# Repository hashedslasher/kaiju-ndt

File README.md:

# Kaiju U-NDT

This is my team's EE senior design project. It is in very early development and will evolve into an autonomous immersion UT device.
The [pic0rick](https://github.com/kelu124/pic0rick) is used for the pulser/receiver, and the V1 Engineering [MPCNC](https://docs.v1e.com/mpcnc/intro) will be used for xyz gantry

The name Kaiju came from a toy that randomly appeared in our lab one day

## Development
   If you are working on this project see [Setup](setup/README.md)

## To run the python scripts

1. **Clone the repo**
   Clone the repo (or download as zip) and cd into kaiju-ndt.

2. **Install Python and dependencies**
   - **Windows:** Download from [python.org](https://www.python.org/downloads/windows/) or run:
     ```bash
     winget install -e --id python.python.3.14
     ```
   - **MacOS:** Download from [python.org](https://www.python.org/downloads/macos/) or run:
     ```bash
     brew install python3
     ```
   - **Linux:** Install python with your package manager:
   
   Debian based:
   ```bash
   sudo apt install python3 python3-pip
   ```
   Arch:
   ```bash
   sudo pacman -S python python-pip
   ```
### Python dependencies
   - Open PowerShell or Terminal and run:
     ```bash
     pip install -r python-tools/requirements.txt
     ```

3. **Flashing the firmware**
   - If the firmware isn't already on the pico, you need to flash it.
   - Hold `BOOTSEL` and plug the board in. It should appear as `RPI-RP2`.
   - Drag and drop `firmware/pico/rp2040.uf2` (Pico) or `firmware/pico/rp2350.uf2` (Pico 2) into the `RPI-RP2` drive.
   - Or with picotool from the root of the repository:
   ```bash
   picotool load firmware/pico/rp2040.uf2
   ```

4. **Run a script**
   In PowerShell or Terminal:
   ```bash
   python3 python-tools/{script_name}.py
   ```

   If you use nix for some reason just:
   ```bash
   nix develop .
   python3 python-tools/{script_name}.py
   ```

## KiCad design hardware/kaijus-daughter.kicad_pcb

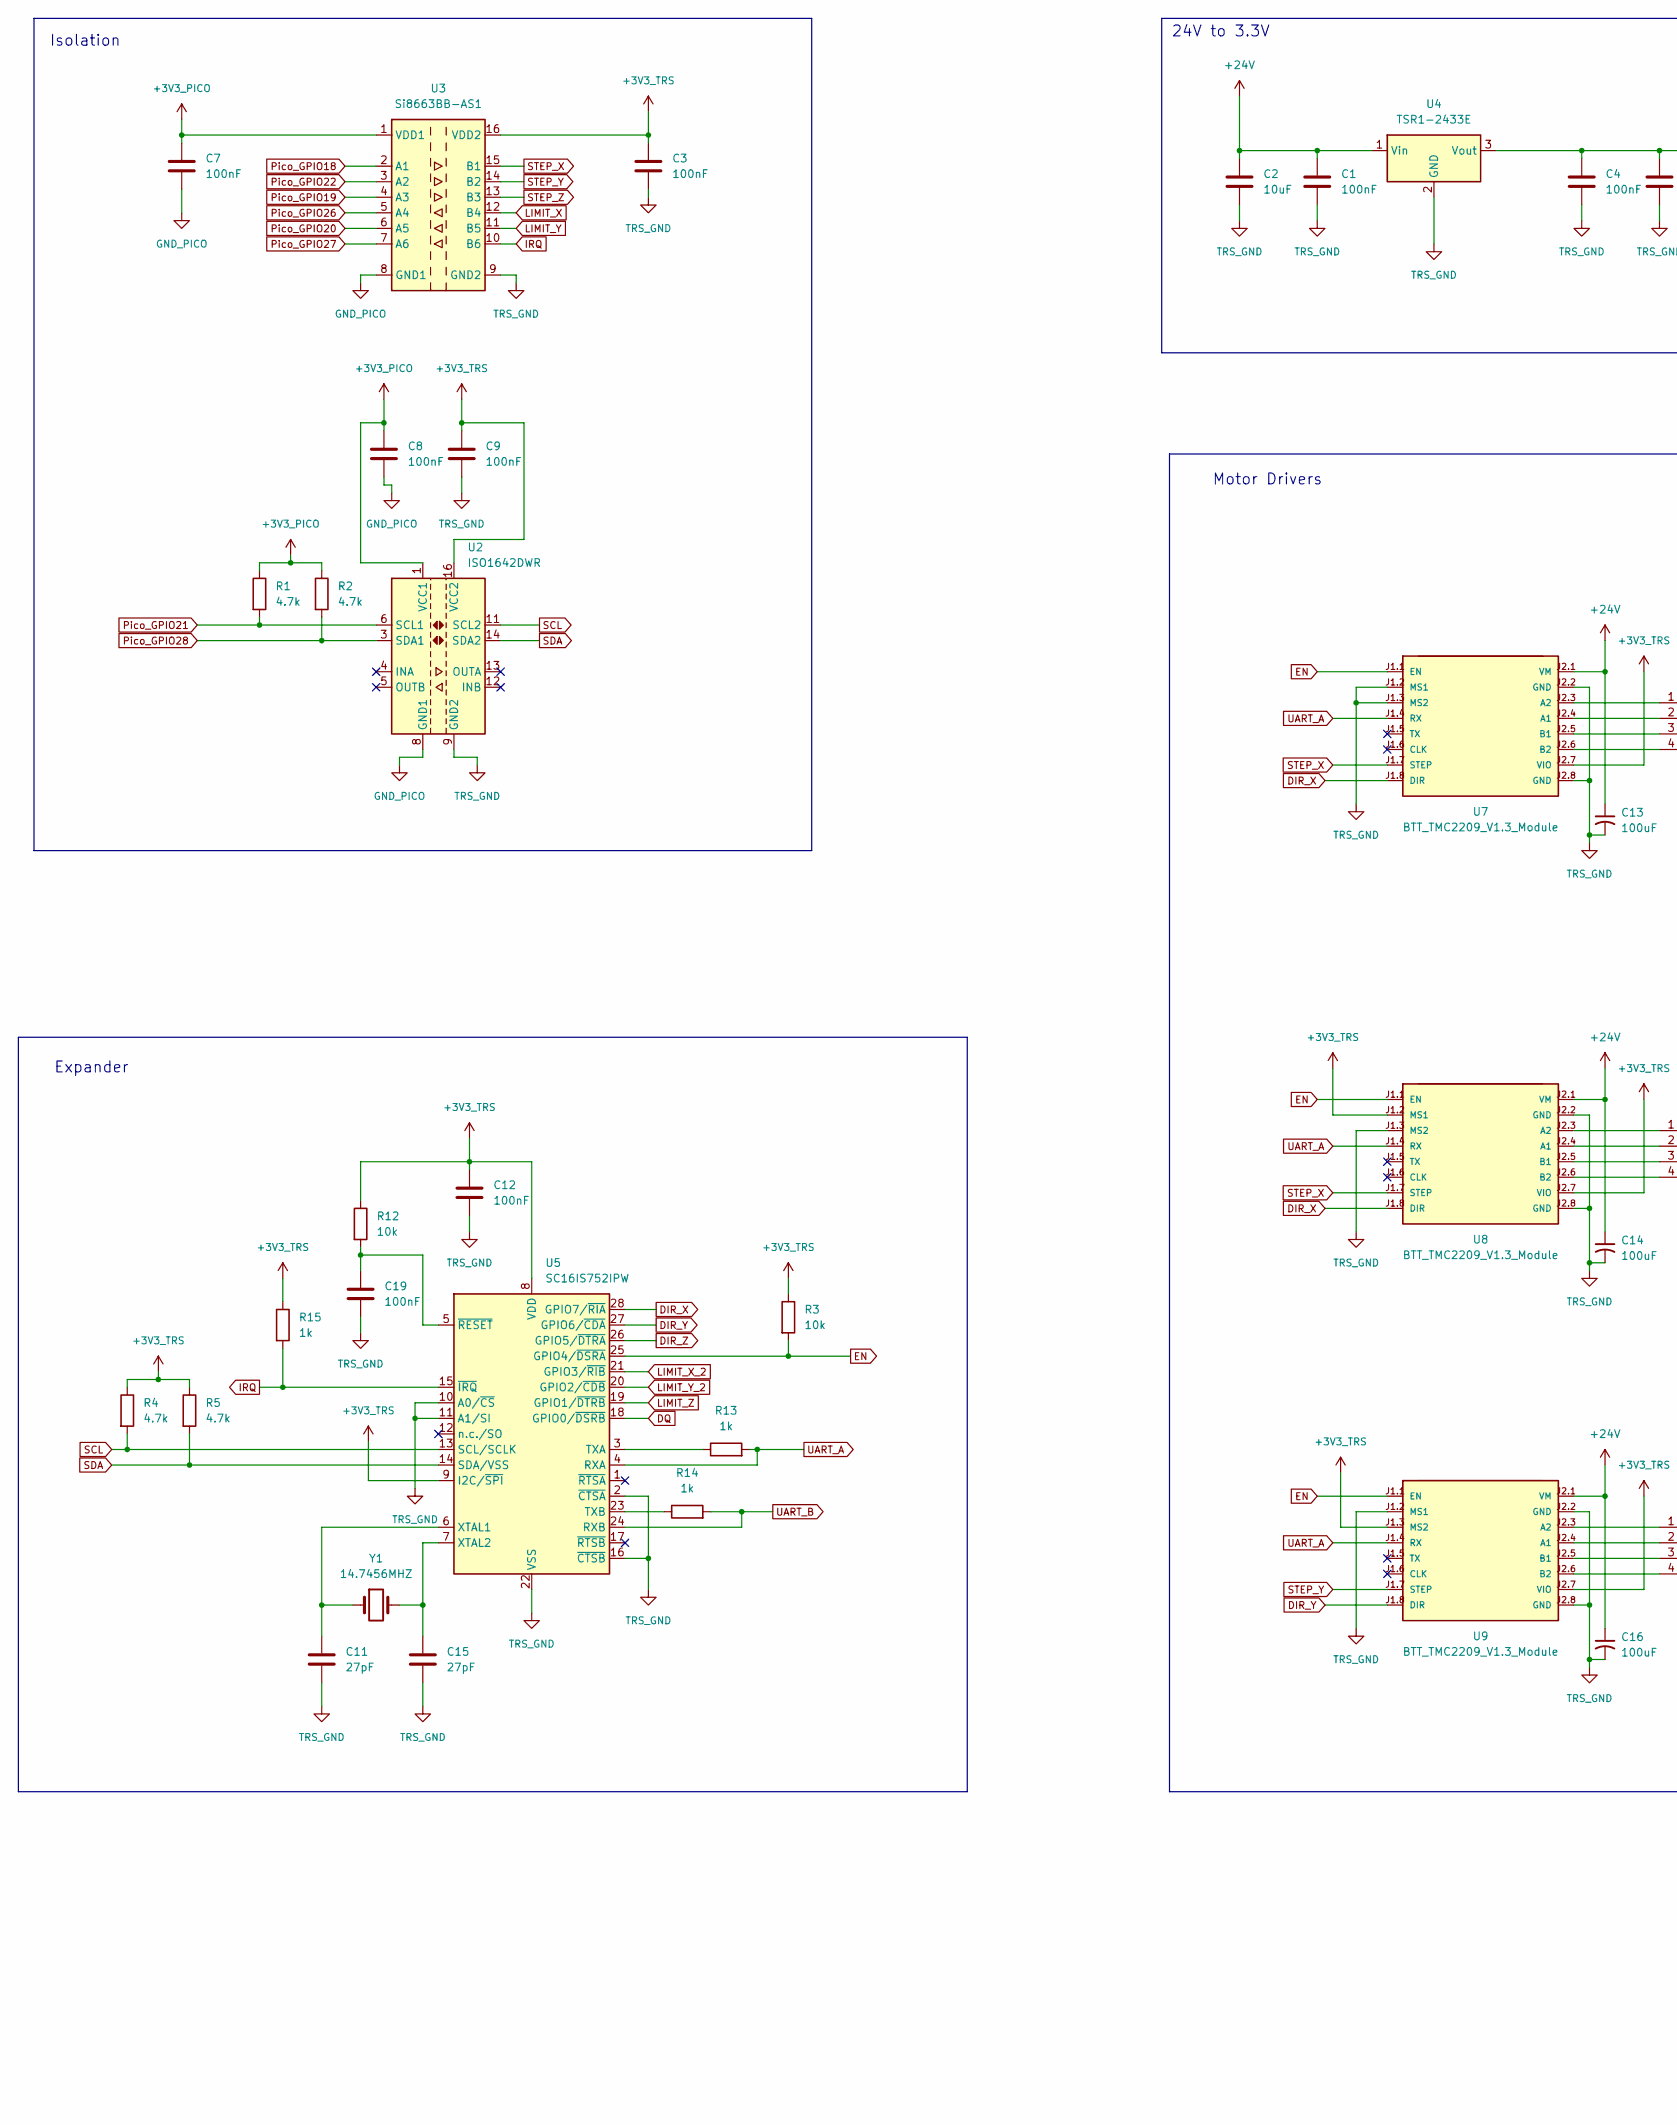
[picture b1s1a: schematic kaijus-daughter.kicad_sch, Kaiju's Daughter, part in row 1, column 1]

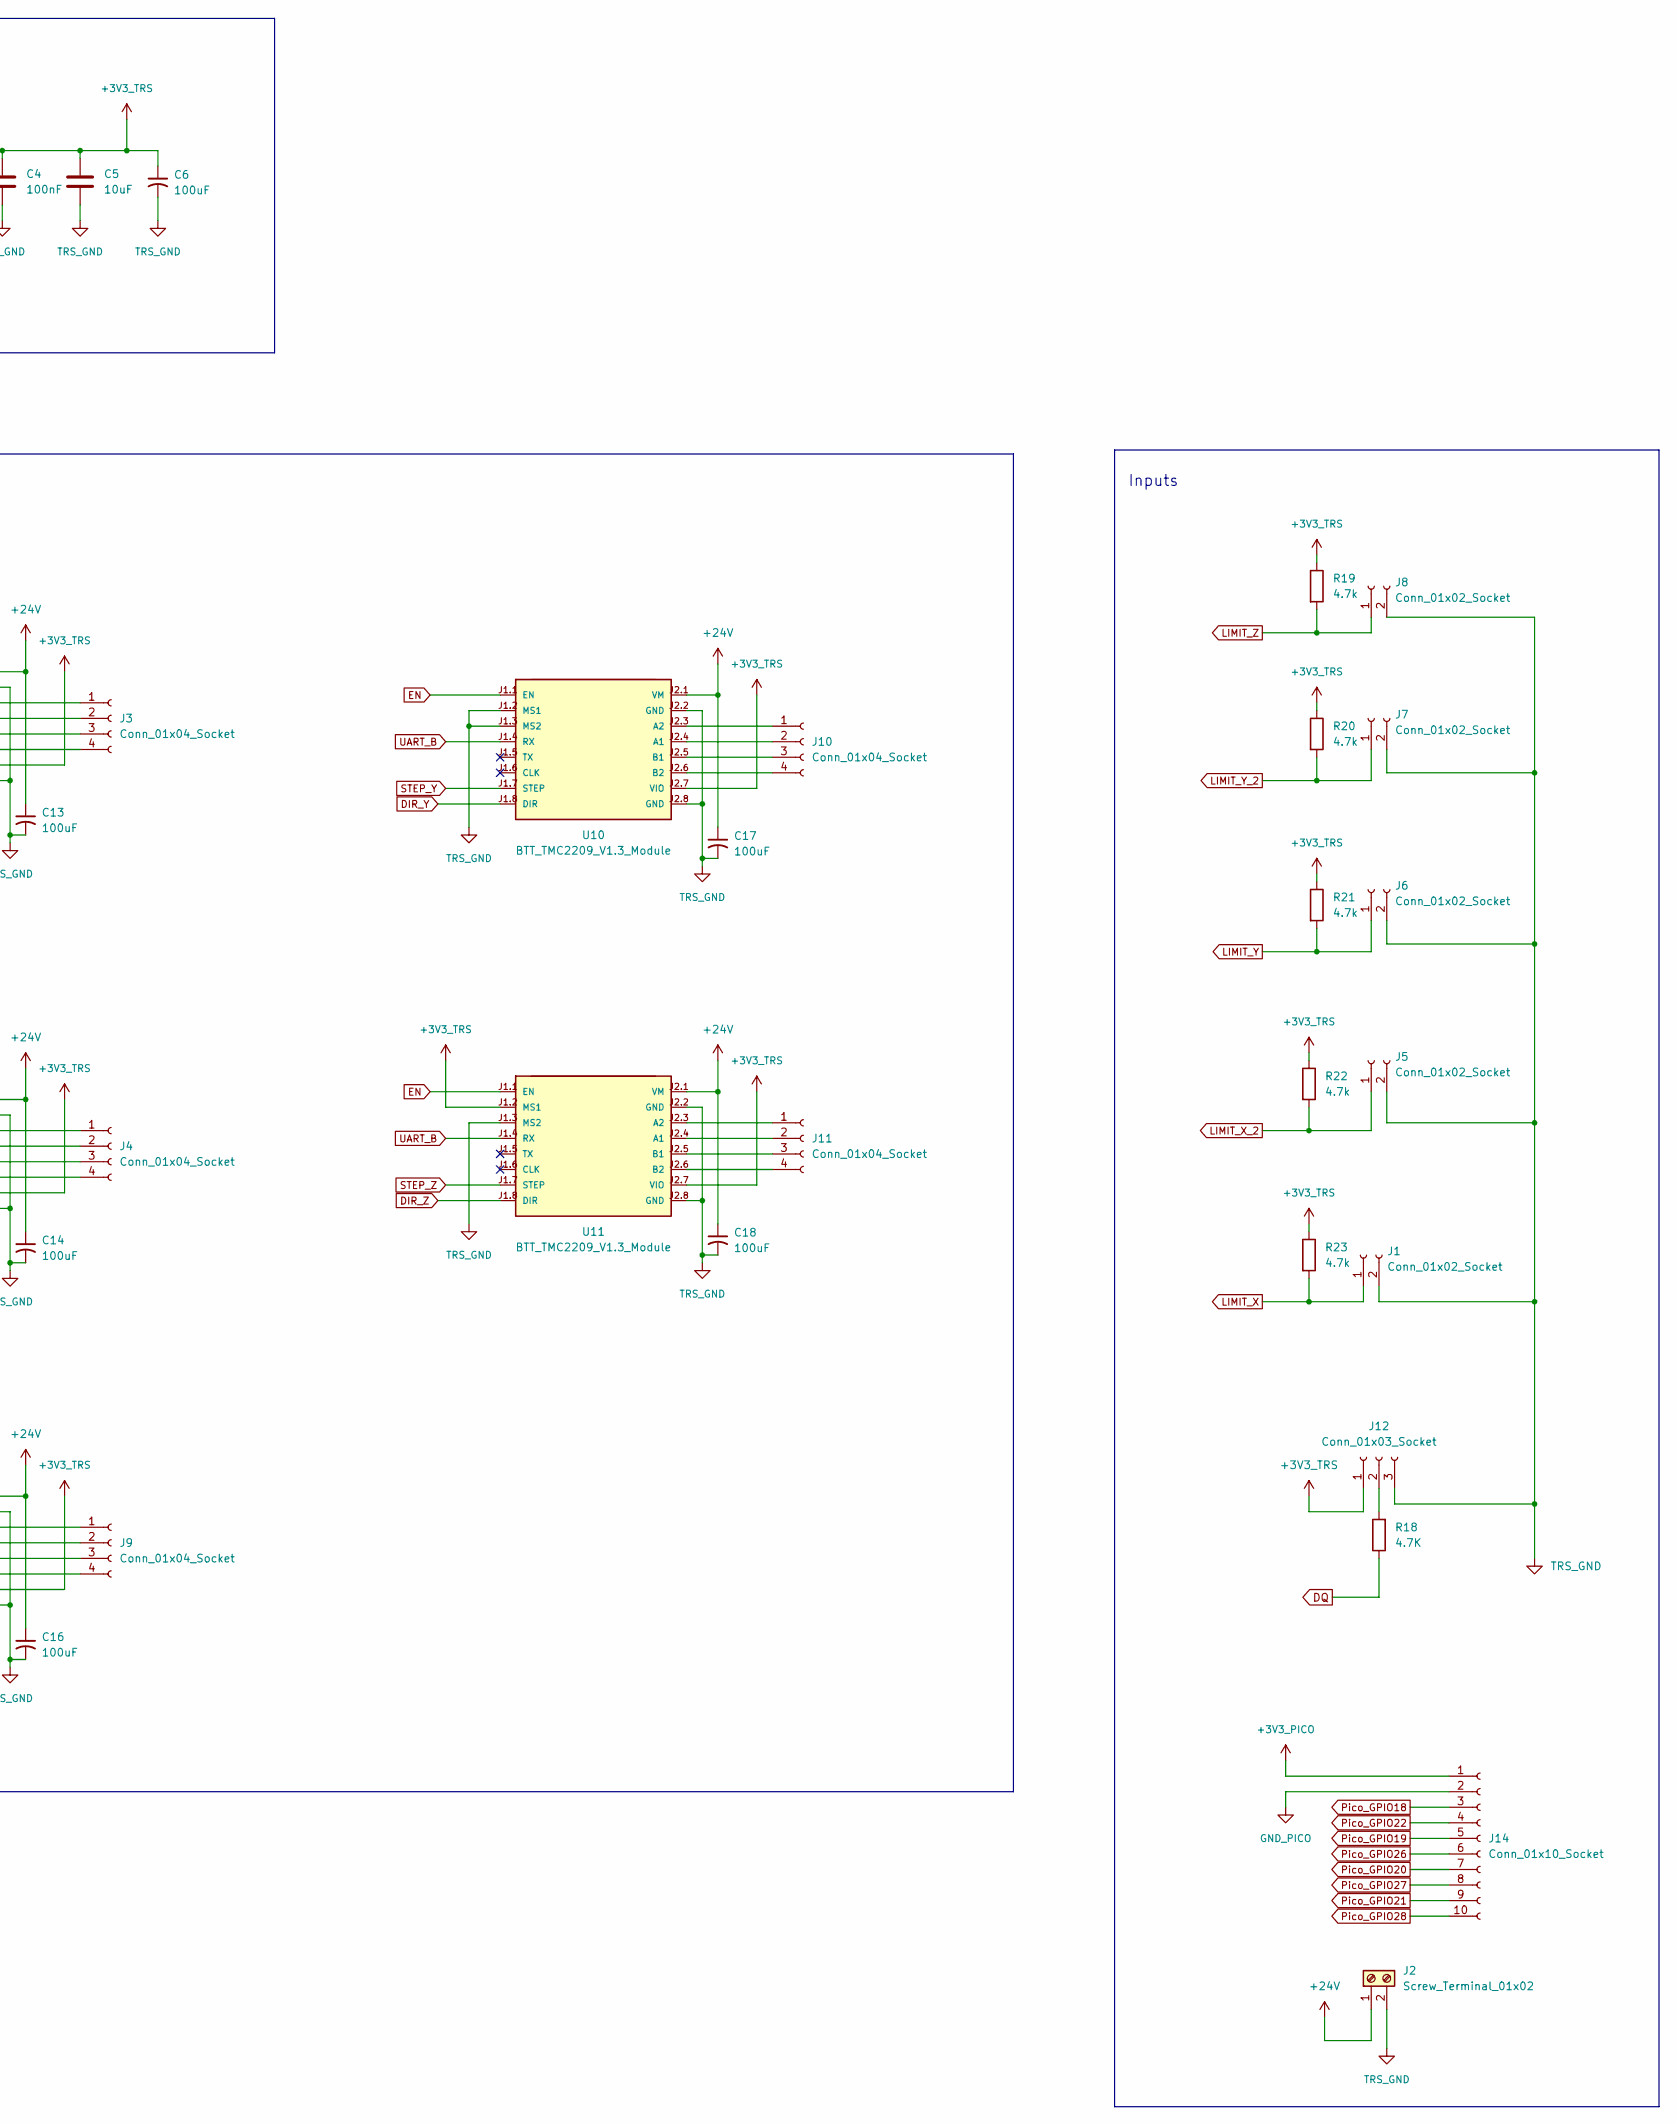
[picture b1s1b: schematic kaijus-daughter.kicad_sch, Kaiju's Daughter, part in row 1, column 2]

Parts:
C1, C3, C4, C7, C8, C9, C12, C19: 100nF; C_0805_2012Metric
C2: 10uF; C_1210_3225Metric
C5: 10uF; C_0805_2012Metric
C6: 100uF; CP_Radial_D5.0mm_P2.00mm
C11, C15: 27pF; C_0805_2012Metric
C13, C14, C16, C17, C18: 100uF; CP_Radial_D8.0mm_P5.00mm
J1, J5, J6, J7, J8: Conn_01x02_Socket; PinHeader_1x02_P2.54mm_Vertical
J2: Screw_Terminal_01x02; TerminalBlock_4Ucon_1x02_P3.50mm_Horizontal
J3, J4, J9, J10, J11: Conn_01x04_Socket; PinHeader_1x04_P2.54mm_Vertical
J12: Conn_01x03_Socket; PinHeader_1x03_P2.54mm_Vertical
J14: Conn_01x10_Socket; PinHeader_1x10_P2.54mm_Vertical
R1, R2, R4, R5, R19, R20, R21, R22, R23: 4.7k; R_0805_2012Metric
R3, R12: 10k; R_0805_2012Metric
R13, R14, R15: 1k; R_0805_2012Metric
R18: 4.7K; R_0805_2012Metric
U2: ISO1642DWR; SOIC-16W_7.5x10.3mm_P1.27mm
U3: Si8663BB-AS1; SOIC-16_3.9x9.9mm_P1.27mm
U4: TSR1-2433E; Converter_DCDC_TRACO_TSR1-xxxxE_THT
U5: SC16IS752IPW; TSSOP-28_4.4x9.7mm_P0.65mm
U7, U8, U9, U10, U11: BTT_TMC2209_V1.3_Module; BTT_TMC2209_V1.3_2x08_P2.54mm
Y1: 14.7456MHZ; Crystal_HC49-U_Vertical

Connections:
+3V3_PICO: C7.1, C8.1, J14.1, R1.1, R2.1, U2.1 (VCC1), U3.1 (VDD1)
+3V3_TRS: C3.1, C4.1, C5.1, C6.1, C9.1, C12.1, J12.1, R3.1, R4.1, R5.1, R12.1, R15.1, R19.1, R20.1, R21.1, R22.1, R23.1, U2.16 (VCC2), U3.16 (VDD2), U4.3 (Vout), U5.8 (VDD), U5.9 (I2C/~SPI), U7.J2.7 (VIO), U8.J1.2 (MS1), U8.J2.7 (VIO), U9.J1.3 (MS2), U9.J2.7 (VIO), U10.J2.7 (VIO), U11.J1.2 (MS1), U11.J2.7 (VIO)
+24V: C1.1, C2.1, C13.1, C14.1, C16.1, C17.1, C18.1, J2.1, U4.1 (Vin), U7.J2.1 (VM), U8.J2.1 (VM), U9.J2.1 (VM), U10.J2.1 (VM), U11.J2.1 (VM)
DIR_X: U5.28 (GPIO7/~RIA), U7.J1.8 (DIR), U8.J1.8 (DIR)
DIR_Y: U5.27 (GPIO6/~CDA), U9.J1.8 (DIR), U10.J1.8 (DIR)
DIR_Z: U5.26 (GPIO5/~DTRA), U11.J1.8 (DIR)
DQ: R18.1, U5.18 (GPIO0/~DSRB)
EN: R3.2, U5.25 (GPIO4/~DSRA), U7.J1.1 (EN), U8.J1.1 (EN), U9.J1.1 (EN), U10.J1.1 (EN), U11.J1.1 (EN)
GND_PICO: C7.2, C8.2, J14.2, U2.8 (GND1), U3.8 (GND1)
IRQ: R15.2, U3.10 (B6), U5.15 (~IRQ)
LIMIT_X: J1.1, R23.2, U3.12 (B4)
LIMIT_X_2: J5.1, R22.2, U5.21 (GPIO3/~RIB)
LIMIT_Y: J6.1, R21.2, U3.11 (B5)
LIMIT_Y_2: J7.1, R20.2, U5.20 (GPIO2/~CDB)
LIMIT_Z: J8.1, R19.2, U5.19 (GPIO1/~DTRB)
unnamed: J3.1, U7.J2.3 (A2)
unnamed: J3.2, U7.J2.4 (A1)
unnamed: J3.3, U7.J2.5 (B1)
unnamed: J3.4, U7.J2.6 (B2)
unnamed: J4.1, U8.J2.3 (A2)
unnamed: J4.2, U8.J2.4 (A1)
unnamed: J4.3, U8.J2.5 (B1)
unnamed: J4.4, U8.J2.6 (B2)
unnamed: J9.1, U9.J2.3 (A2)
unnamed: J9.2, U9.J2.4 (A1)
unnamed: J9.3, U9.J2.5 (B1)
unnamed: J9.4, U9.J2.6 (B2)
unnamed: J10.1, U10.J2.3 (A2)
unnamed: J10.2, U10.J2.4 (A1)
unnamed: J10.3, U10.J2.5 (B1)
unnamed: J10.4, U10.J2.6 (B2)
unnamed: J11.1, U11.J2.3 (A2)
unnamed: J11.2, U11.J2.4 (A1)
unnamed: J11.3, U11.J2.5 (B1)
unnamed: J11.4, U11.J2.6 (B2)
unnamed: J12.2, R18.2
unnamed: R13.1, U5.3 (TXA)
unnamed: R14.1, U5.23 (TXB)
unnamed: C11.1, U5.6 (XTAL1), Y1.1
unnamed: C15.1, U5.7 (XTAL2), Y1.2
unnamed: C19.1, R12.2, U5.5 (~RESET)
Pico_GPIO18: J14.3, U3.2 (A1)
Pico_GPIO19: J14.5, U3.4 (A3)
Pico_GPIO20: J14.7, U3.6 (A5)
Pico_GPIO21: J14.9, R1.2, U2.6 (SCL1)
Pico_GPIO22: J14.4, U3.3 (A2)
Pico_GPIO26: J14.6, U3.5 (A4)
Pico_GPIO27: J14.8, U3.7 (A6)
Pico_GPIO28: J14.10, R2.2, U2.3 (SDA1)
SCL: R4.2, U2.11 (SCL2), U5.13 (SCL/SCLK)
SDA: R5.2, U2.14 (SDA2), U5.14 (SDA/VSS)
STEP_X: U3.15 (B1), U7.J1.7 (STEP), U8.J1.7 (STEP)
STEP_Y: U3.14 (B2), U9.J1.7 (STEP), U10.J1.7 (STEP)
STEP_Z: U3.13 (B3), U11.J1.7 (STEP)
TRS_GND: C1.2, C2.2, C3.2, C4.2, C5.2, C6.2, C9.2, C11.2, C12.2, C13.2, C14.2, C15.2, C16.2, C17.2, C18.2, C19.2, J1.2, J2.2, J5.2, J6.2, J7.2, J8.2, J12.3, U2.9 (GND2), U3.9 (GND2), U4.2 (GND), U5.2 (~CTSA), U5.10 (A0/~CS), U5.11 (A1/SI), U5.16 (~CTSB), U5.22 (VSS), U7.J1.2 (MS1), U7.J1.3 (MS2), U7.J2.2 (GND), U7.J2.8 (GND), U8.J1.3 (MS2), U8.J2.2 (GND), U8.J2.8 (GND), U9.J1.2 (MS1), U9.J2.2 (GND), U9.J2.8 (GND), U10.J1.2 (MS1), U10.J1.3 (MS2), U10.J2.2 (GND), U10.J2.8 (GND), U11.J1.3 (MS2), U11.J2.2 (GND), U11.J2.8 (GND)
UART_A: R13.2, U5.4 (RXA), U7.J1.4 (RX), U8.J1.4 (RX), U9.J1.4 (RX)
UART_B: R14.2, U5.24 (RXB), U10.J1.4 (RX), U11.J1.4 (RX)

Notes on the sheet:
Expander
Inputs
Isolation
Motor Drivers
24V to 3.3V

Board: 2 copper layers, 56 parts (0 on the bottom side), 57 nets, no tracks yet.

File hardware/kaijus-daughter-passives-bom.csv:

Part Number,Amount,Value,PCB Label,KiCad Footprint
RC0805FR-071KL,3,"1 kΩ, 1%, 0805","R13, R14, R15",Resistor_SMD:R_0805_2012Metric
RC0805FR-074K7L,10,"4.7 kΩ, 1%, 0805","R1, R2, R4, R5, R18, R19, R20, R21, R22, R23",Resistor_SMD:R_0805_2012Metric
RC0805FR-0710KL,2,"10 kΩ, 1%, 0805","R3, R12",Resistor_SMD:R_0805_2012Metric
CL21B104KBCNFNC,8,"100 nF, 50 V, X7R, 0805","C1, C3, C4, C7, C8, C9, C12, C19",Capacitor_SMD:C_0805_2012Metric
CL32B106KBJZW6E,1,"10 µF, 50 V, X7R, 1210",C2,Capacitor_SMD:C_1210_3225Metric
TMK212BBJ106MG-T,1,"10 µF, 25 V, X5R, 0805",C5,Capacitor_SMD:C_0805_2012Metric
ESK107M016AC3AA,1,"100 µF, 16 V, electrolytic, THT",C6,Capacitor_THT:CP_Radial_D5.0mm_P2.00mm
EEU-FR1H101B,5,"100 µF, 50 V, electrolytic, THT","C13, C14, C16, C17, C18",Capacitor_THT:CP_Radial_D8.0mm_P5.00mm
C0805C270J5GACTU,2,"27 pF, 50 V, C0G, 0805","C11, C15",Capacitor_SMD:C_0805_2012Metric
